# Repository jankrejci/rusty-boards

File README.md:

# Rusty Boards

Monorepo for ESP32 sensor boards and supporting services. KiCAD hardware
designs with embedded Rust firmware, plus a host-side metrics server.

Boards export Prometheus metrics over USB serial. The sensor-server collects
them and serves a combined `/metrics` endpoint for Prometheus scraping.

## Repository structure

```
boards/
  voltage-meter/        Voltage + temp + LCD board
    pcb/                KiCAD schematic and PCB
    firmware/           Embedded Rust (esp-hal, embassy)
  temp-sensor/          DS18B20 temperature sensor board
    firmware/           Embedded Rust (esp-hal, embassy)
  dummy-button/         Rotary encoder + USB-C power board
    pcb/                KiCAD schematic and PCB
    firmware/           Embedded Rust (esp-hal, embassy)
tools/
  sensor-server/        Host-side HTTP server bridging serial to Prometheus
lib/
  kicad/                Shared KiCAD symbols, footprints, and 3D models
```

## Boards

### voltage-meter

ADC voltage measurement with calibration curve and Kalman filter, LM75
temperature sensor over I2C, ST7735s 160x80 LCD display over SPI. Embassy
async tasks for reading, display, metrics export, and watchdog.

### temp-sensor

DS18B20 OneWire temperature sensors driven via the ESP32-C3 RMT peripheral.
Embassy async tasks for sensor reading, metrics export, and watchdog.

### dummy-button

Rotary encoder (PEC11R) with push button and TP5400 USB-C charging/boost
converter. ESP32-S3 (Xtensa) with hello world firmware.

## Tools

### sensor-server

HTTP server that auto-detects ESP32-C3 boards on USB (VID `0x303a`, PID
`0x1001`), reads Prometheus-formatted metrics from serial, and serves them on
`GET /metrics`. Uses inotify for instant device hot-plug detection.

## Hardware platform

Most boards use ESP32-C3 (RISC-V). dummy-button uses ESP32-S3 (Xtensa).

- ESP32-C3: target `riscv32imc-unknown-none-elf`, stable Rust, `build-std = ["core"]`
- ESP32-S3: target `xtensa-esp32s3-none-elf`, espup Xtensa toolchain
- Dev board: ESP32-C3 Super Mini, USB-JTAG on `/dev/ttyACM0`
- Flash/debug: probe-rs

## Development

Each project has its own nix flake with dev shells and checks.

```sh
cd boards/temp-sensor && nix develop     # firmware dev shell
cd boards/voltage-meter && nix develop   # firmware dev shell
cd boards/dummy-button && nix develop    # Xtensa firmware dev shell
cd boards/dummy-button && nix develop .#hardware  # KiCAD shell
cd tools/sensor-server && nix develop    # Rust dev shell
```

### Firmware workflow

```sh
cd boards/temp-sensor
nix develop
cd firmware
cargo build --release       # build
cargo run --release         # build + flash + monitor via probe-rs
```

### Static builds (sensor-server)

```sh
cd tools/sensor-server
nix develop .#x86_64-static     # x86_64 musl
nix develop .#aarch64-static    # aarch64 musl cross
cargo build --release
```

### Checks

Each flake defines checks that run with `nix flake check`:

| Project | Checks |
|---------|--------|
| `tools/sensor-server` | clippy, fmt, test |
| `boards/temp-sensor` | clippy, fmt |
| `boards/voltage-meter` | clippy, fmt, DRC, ERC |
| `boards/dummy-button` | DRC, ERC |

Cargo checks use [crane](https://github.com/ipetkov/crane). KiCAD checks use
`kicad-cli` for design rule checking (DRC) and electrical rule checking (ERC).

## Metrics format

All boards emit Prometheus text format over USB serial:

```
metric_name{label="value"} 42.0 1709500000000
```

The sensor-server validates, timestamps, and aggregates these lines for
Prometheus scraping.

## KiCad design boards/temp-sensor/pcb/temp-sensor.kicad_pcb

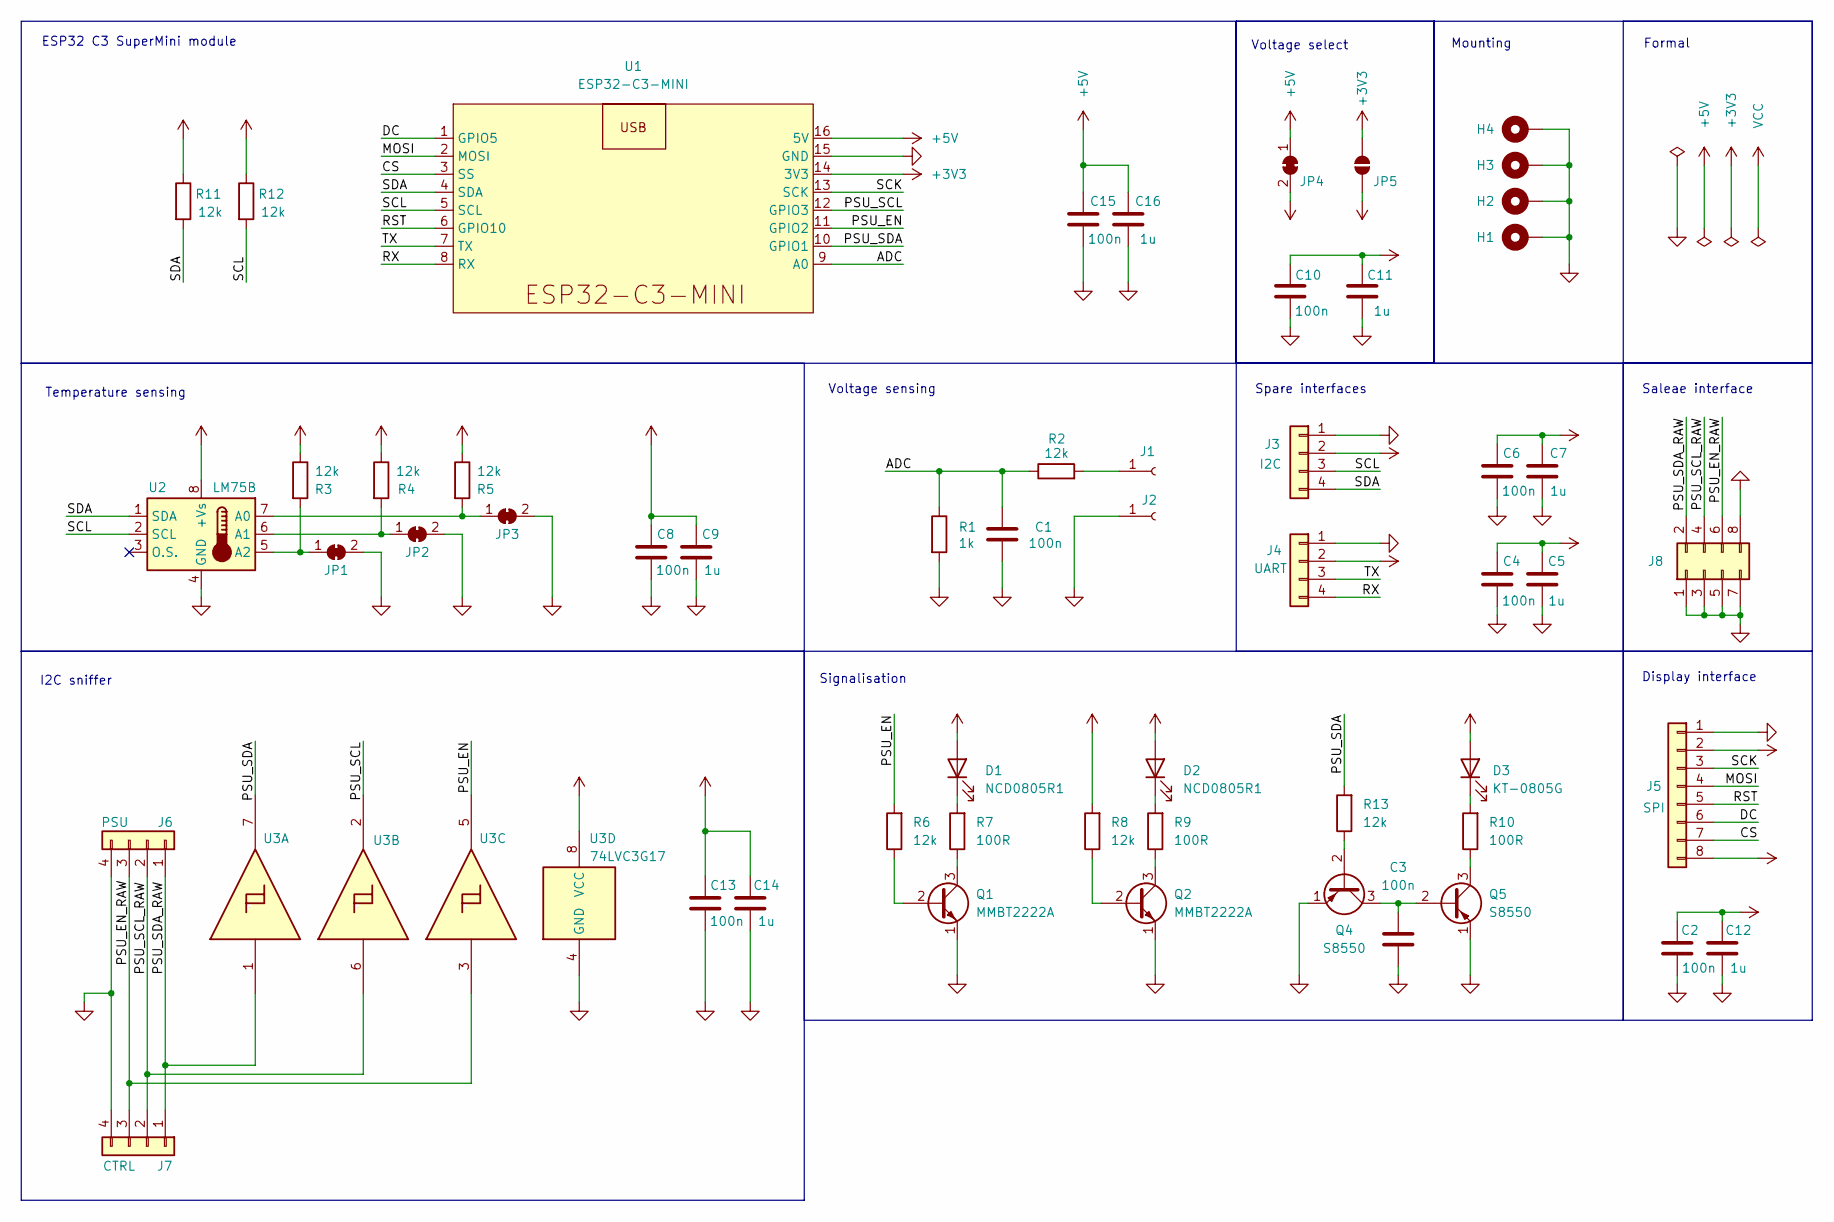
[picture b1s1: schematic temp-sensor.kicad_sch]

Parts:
C1, C2, C3, C4, C6, C8, C10, C13, C15: 100n; C_0603_1608Metric_Pad1.08x0.95mm_HandSolder; LCSC C14663
C5, C7: 1u; C_0603_1608Metric_Pad1.08x0.95mm_HandSolder; LCSC C59302
C9, C11, C12, C14, C16: 1u; C_0603_1608Metric_Pad1.08x0.95mm_HandSolder; LCSC C15849
D1, D2: NCD0805R1; LED_0805_2012Metric_Pad1.15x1.40mm_HandSolder; LCSC C84256
D3: KT-0805G; LED_0805_2012Metric_Pad1.15x1.40mm_HandSolder; LCSC C2297
H1, H2, H3, H4: M3_Pad_Via; MountingHole_3.2mm_M3_DIN965_Pad_TopBottom
J1: Bannana plug; Banana_Cliff_FCR7350R_S16N-PC_Horizontal
J2: Bannana plug; Banana_Cliff_FCR7350B_S16N-PC_Horizontal
J3: I2C; PinHeader_1x04_P2.54mm_Vertical
J4: UART; PinHeader_1x04_P2.54mm_Vertical
J5: SPI; PinHeader_1x08_P2.54mm_Vertical
J6: PSU; Molex_KK-254_AE-6410-04A_1x04_P2.54mm_Vertical
J7: CTRL; Molex_KK-254_AE-6410-04A_1x04_P2.54mm_Vertical
J8: Conn_02x08_Odd_Even; PinHeader_2x04_P2.54mm_Vertical
JP1, JP2, JP3, JP4: SolderJumper_2_Bridged; SolderJumper-2_P1.3mm_Bridged_RoundedPad1.0x1.5mm
JP5: SolderJumper_2_Open; SolderJumper-2_P1.3mm_Open_RoundedPad1.0x1.5mm
Q1, Q2: MMBT2222A; SOT-23; LCSC C8512
Q4, Q5: S8550; SOT-23; LCSC C105432
R1: 1k; R_0603_1608Metric_Pad0.98x0.95mm_HandSolder; LCSC C21190
R2, R3, R4, R5, R6, R8, R11, R12, R13: 12k; R_0603_1608Metric_Pad0.98x0.95mm_HandSolder; LCSC C22790
R7, R9, R10: 100R; R_0603_1608Metric_Pad0.98x0.95mm_HandSolder; LCSC C22775
U1: ESP32-C3-MINI; ESP32-C3-DevKitC-02
U2: LM75B; SOIC-8_3.9x4.9mm_P1.27mm; LCSC C725792
U3: 74LVC3G17; VSSOP-8_2.3x2mm_P0.5mm; LCSC C68245

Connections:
+3V3: JP5.2 (B), U1.14 (3V3)
+5V: C15.2, C16.2, JP4.1 (A), U1.16 (5V)
/ADC: C1.2, R1.1, R2.1, U1.9 (A0)
/CS: J5.7, U1.3 (SS)
/DC: J5.6, U1.1 (GPIO5)
/MOSI: J5.4, U1.2 (MOSI)
/PSU_EN: R6.2, U1.11 (GPIO2), U3.5
/PSU_EN_RAW: J6.3, J7.3, J8.6, U3.3
/PSU_SCL: U1.12 (GPIO3), U3.2
/PSU_SCL_RAW: J6.2, J7.2, J8.4, U3.6
/PSU_SDA: R13.2, U1.10 (GPIO1), U3.7
/PSU_SDA_RAW: J6.1, J7.1, J8.2, U3.1
/RST: J5.5, U1.6 (GPIO10)
/RX: J4.4, U1.8 (RX)
/SCK: J5.3, U1.13 (SCK)
/SCL: J3.3, R12.2, U1.5 (SCL), U2.2 (SCL)
/SDA: J3.4, R11.2, U1.4 (SDA), U2.1 (SDA)
/TX: J4.3, U1.7 (TX)
GND: C1.1, C2.1, C3.2, C4.1, C5.1, C6.1, C7.1, C8.1, C9.1, C10.1, C11.1, C12.1, C13.1, C14.1, C15.1, C16.1, H1.1, H2.1, H3.1, H4.1, J2.1, J3.1, J4.1, J5.1, J6.4, J7.4, J8.1, J8.3, J8.5, J8.7, J8.8, JP1.2 (B), JP2.2 (B), JP3.2 (B), Q1.1 (E), Q2.1 (E), Q4.1 (E), Q5.1 (E), R1.2, U1.15 (GND), U2.4 (GND), U3.4 (GND)
unnamed: D1.1 (K), R7.2
unnamed: D2.1 (K), R9.2
unnamed: D3.1 (K), R10.2
unnamed: J1.1, R2.2
unnamed: JP1.1 (A), R3.2, U2.5 (A2)
unnamed: JP2.1 (A), R4.2, U2.6 (A1)
unnamed: JP3.1 (A), R5.2, U2.7 (A0)
unnamed: Q1.2 (B), R6.1
unnamed: Q1.3 (C), R7.1
unnamed: Q2.2 (B), R8.1
unnamed: Q2.3 (C), R9.1
unnamed: Q4.2 (B), R13.1
unnamed: C3.1, Q4.3 (C), Q5.2 (B)
unnamed: Q5.3 (C), R10.1
VCC: C2.2, C4.2, C5.2, C6.2, C7.2, C8.2, C9.2, C10.2, C11.2, C12.2, C13.2, C14.2, D1.2 (A), D2.2 (A), D3.2 (A), J3.2, J4.2, J5.2, J5.8, JP4.2 (B), JP5.1 (A), R3.1, R4.1, R5.1, R8.2, R11.1, R12.1, U2.8 (+Vs), U3.8 (VCC)

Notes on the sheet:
Saleae interface
Signalisation
ESP32 C3 SuperMini module
Voltage sensing
I2C sniffer
Display interface
Voltage select
Formal
Spare interfaces
Mounting
Temperature sensing

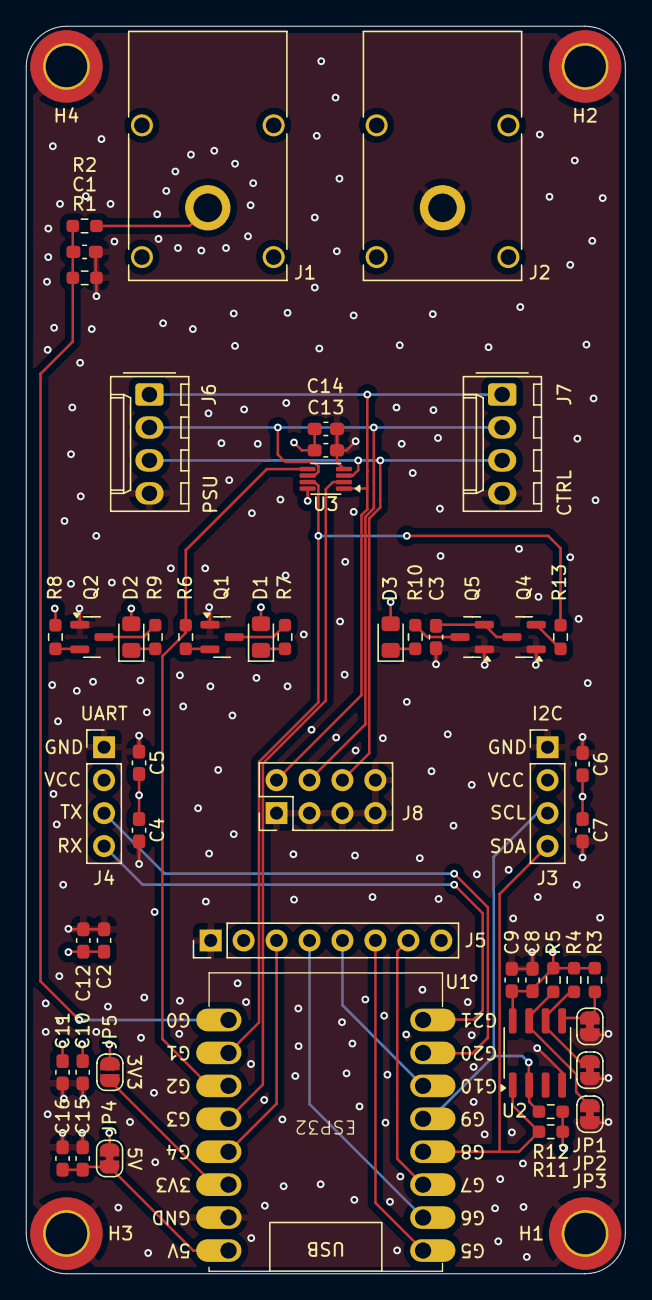
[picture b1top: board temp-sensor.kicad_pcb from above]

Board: 4 copper layers, 46.2 x 96.2 mm, 56 parts (0 on the bottom side), 34 nets.

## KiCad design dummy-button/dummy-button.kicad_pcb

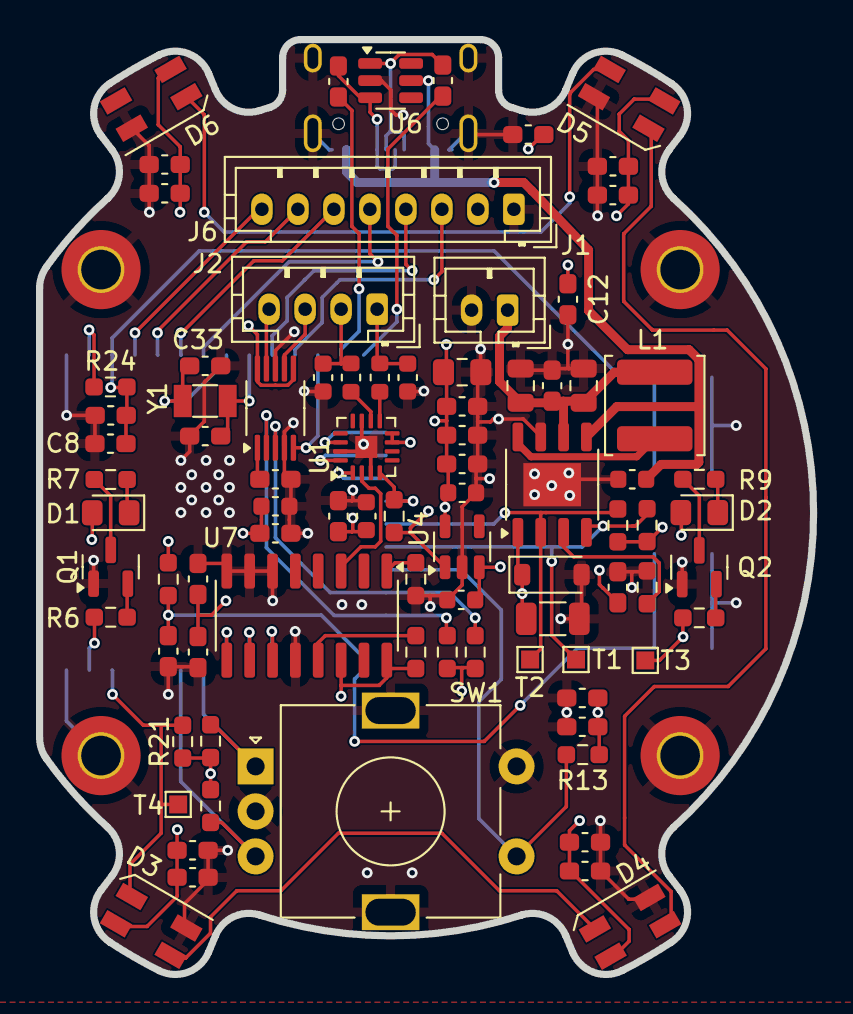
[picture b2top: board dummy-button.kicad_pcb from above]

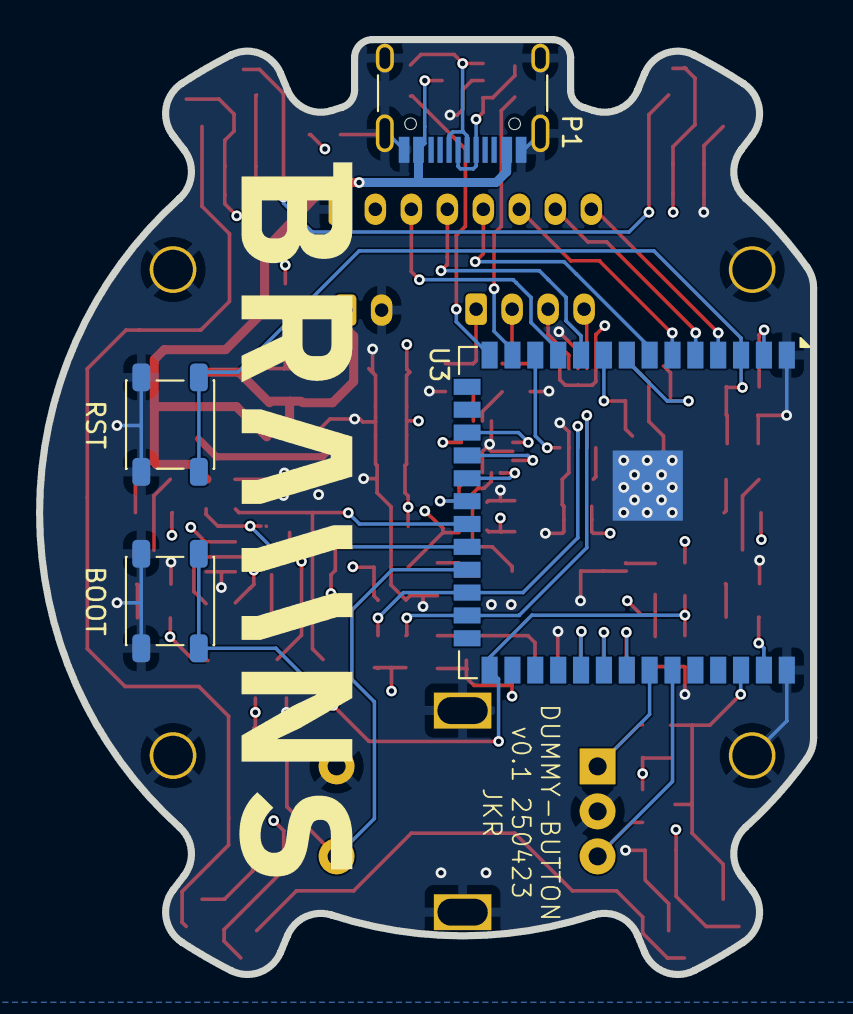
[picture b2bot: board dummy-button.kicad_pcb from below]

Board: 4 copper layers, 43.0 x 51.9 mm, 93 parts (4 on the bottom side), 57 nets.

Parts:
C2, C3, C4, C5, C6, C7, C8, C9, C10, C21, C22, C23, C24, C25, C30, C32: 100n; C_0603_1608Metric_Pad1.08x0.95mm_HandSolder
C12, C13, C14, C15, C16, C17, C18, C19, C28: 1u; C_0603_1608Metric_Pad1.08x0.95mm_HandSolder
C20: 4u7; C_0805_2012Metric_Pad1.18x1.45mm_HandSolder
C26, C29: 22u; C_0805_2012Metric
C27: 100u; C_1206_3216Metric
C31, C34, C35, C36, C39: 10u; C_0603_1608Metric
C33, C40: 12p; C_0603_1608Metric_Pad1.08x0.95mm_HandSolder
C37, C38: 220p; C_0603_1608Metric
D1, D2: NCD0805R1; LED_0805_2012Metric_Pad1.15x1.40mm_HandSolder
D3, D4, D5, D6: WS2812B; LED_SK6812MINI_PLCC4_3.5x3.5mm_P1.75mm
D7: TVS; D_SOD-123
FB1, FB2: FerriteBead_Small; L_0603_1608Metric
H1, H2, H3, H4: M2_Pad_Via; MountingHole_2.2mm_M2_Pad_TopOnly
J1: Batt; JST_PH_B2B-PH-K_1x02_P2.00mm_Vertical
J2: repro_motor; JST_PH_B4B-PH-K_1x04_P2.00mm_Vertical
J6: LCD; JST_PH_B8B-PH-K_1x08_P2.00mm_Vertical
L1: 10u; L_Sunlord_SWPA5040S
P1: USB_C_Plug_USB2.0; USB_C_Receptacle_HRO_TYPE-C-31-M-12
Q1, Q2: MMBT2222A; SOT-23
R6, R8, R11, R12, R13, R14, R15, R16, R19, R20, R21, R23, R24, R27: 12k; R_0603_1608Metric_Pad0.98x0.95mm_HandSolder
R7, R9: 100R; R_0603_1608Metric_Pad0.98x0.95mm_HandSolder
R17, R18: 10R; C_0603_1608Metric_Pad1.08x0.95mm_HandSolder
R25, R26: 100k; R_0603_1608Metric_Pad0.98x0.95mm_HandSolder
SW1: RotaryEncoder_Switch_MP; RotaryEncoder_Alps_EC11E-Switch_Vertical_H20mm
SW2: RST; SW_SPST_PTS647_Sx38
SW3: BOOT; SW_SPST_PTS647_Sx38
T1, T2, T3, T4: TestPoint; TestPoint_Pad_1.0x1.0mm
U1: MAX98357A; TQFN-16-1EP_3x3mm_P0.5mm_EP1.23x1.23mm
U2: TP5400; HTSOP-8-1EP_3.9x4.9mm_P1.27mm_EP2.4x3.2mm
U3: ESP32-S3-WROOM-1
U4: TLV75533PDBV; SOT-23-5
U5: DRV2605LDGS; VSSOP-10_3x3mm_P0.5mm
U6: ESDU5V0H4; SOT-23-6
U7: CD4051B; SOIC-16_3.9x9.9mm_P1.27mm
Y1: 32.768 kHz; Crystal_SMD_3215-2Pin_3.2x1.5mm

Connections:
+3V3: C2.2, C3.2, C12.2, C13.2, C20.1, C21.1, C22.1, C23.1, C35.1, J6.2, R8.2, R11.1, R12.1, R13.1, R14.1, R15.1, R16.1, R20.1, R21.1, R24.1, R27.1, T3.1, U3.2 (3V3), U4.5 (OUT)
+5V: C4.2, C5.2, C6.2, C7.2, C9.2, C14.2, C15.2, C16.2, C17.2, C25.1, C27.1, C28.2, C30.1, C32.1, C34.1, C36.1, C39.1, D1.2 (A), D2.2 (A), D3.4 (VDD), D4.4 (VDD), D5.4 (VDD), D6.4 (VDD), D7.1 (K), R23.1, R25.2, U1.7 (VDD), U1.8 (VDD), U2.1 (VOUT), U4.1 (IN), U4.3 (EN), U5.6 (VDD/NC), U5.10 (VDD), U7.14 (X1), U7.16 (VDD)
/CPU/BAT_CHRG: R20.2, T2.1, U2.2 (CHRG), U3.21 (IO13)
/CPU/BAT_STDBY: R16.2, T1.1, U2.4 (STDBY), U3.22 (IO14)
/CPU/BOOT: C10.1, R27.2, SW3.1, U3.27 (IO0)
/CPU/DM: R18.1, U3.13 (USB_D-)
/CPU/DP: R17.1, U3.14 (USB_D+)
/CPU/EN: C8.1, C19.1, R24.2, SW2.1, U3.3 (EN)
/CPU/GAIN_A: U3.31 (IO38), U7.11 (A)
/CPU/GAIN_B: U3.32 (IO39), U7.10 (B)
/CPU/GAIN_C: U3.33 (IO40), U7.9 (C)
/CPU/HEARTBEAT: R6.2, U3.39 (IO1)
/CPU/LCD_BLK: J6.8, U3.4 (IO4)
/CPU/LCD_CS: J6.7, U3.5 (IO5)
/CPU/LCD_DC: J6.6, U3.6 (IO6)
/CPU/LCD_MOSI: J6.4, U3.10 (IO17)
/CPU/LCD_RST: J6.5, U3.7 (IO7)
/CPU/LCD_SCK: J6.3, U3.11 (IO18)
/CPU/LED_BUS: D3.3 (DIN), R21.2, T4.1, U3.38 (IO2)
/CPU/MOTOR_EN: U3.12 (IO8), U5.5 (EN)
/CPU/REPRO_CLK: U1.16 (BCLK), U3.18 (IO10)
/CPU/REPRO_SD: U1.1 (DIN), U3.19 (IO11)
/CPU/REPRO_SD_MODE: R23.2, U1.4 (~SD_MODE), U3.20 (IO12)
/CPU/REPRO_WS: U1.14 (LRCLK), U3.17 (IO9)
/CPU/ROT_A: R14.2, SW1.A, U3.34 (IO41)
/CPU/ROT_B: R15.2, SW1.B, U3.35 (IO42)
/CPU/ROT_SW: R13.2, SW1.S1, U3.23 (IO21)
/CPU/SCL: R12.2, U3.25 (IO48), U5.2 (SCL)
/CPU/SDA: R11.2, U3.24 (IO47), U5.3 (SDA)
/CPU/XTAL_A: C33.2, U3.8 (IO15), Y1.2
/CPU/XTAL_B: C40.2, U3.9 (IO16), Y1.1
/Peripherals/MOTOR_N: J2.4, U5.9 (OUT-)
/Peripherals/MOTOR_P: J2.3, U5.7 (OUT+)
/Peripherals/REPRO_GAIN: U1.2 (GAIN_SLOT), U7.3 (X)
/Peripherals/REPRO_N: C38.1, FB1.1, J2.2
/Peripherals/REPRO_P: C37.1, FB2.1, J2.1
GND: C2.1, C3.1, C4.1, C5.1, C6.1, C7.1, C8.2, C9.1, C10.2, C12.1, C13.1, C14.1, C15.1, C16.1, C17.1, C18.1, C19.2, C20.2, C21.2, C22.2, C23.2, C24.2, C25.2, C26.2, C27.2, C28.1, C29.2, C30.2, C31.2, C32.2, C33.1, C34.2, C35.2, C36.2, C37.2, C38.2, C39.2, C40.1, D3.2 (VSS), D4.2 (VSS), D5.2 (VSS), D6.2 (VSS), D7.2 (A), H1.1, H2.1, H3.1, H4.1, J1.2, J6.1, P1.A1 (GND), P1.A12 (GND), P1.B1 (GND), P1.B12 (GND), P1.S1 (SHIELD), Q1.1 (E), Q2.1 (E), R19.2, R26.2, SW1.C, SW1.MP, SW1.S2, SW2.2, SW3.2, U1.3 (GND), U1.11 (GND), U1.15 (GND), U1.17 (PAD), U2.7 (GND), U2.9 (PAD), U3.1 (GND), U3.40 (GND), U3.41 (GND), U4.2 (GND), U5.4 (IN/TRIG), U5.8 (GND), U6.2 (GND), U7.6 (INH), U7.7 (VEE), U7.8 (VSS), U7.12 (X3)
unnamed: D1.1 (K), R7.2
unnamed: D2.1 (K), R9.2
unnamed: D3.1 (DOUT), D4.3 (DIN)
unnamed: D4.1 (DOUT), D5.3 (DIN)
unnamed: D5.1 (DOUT), D6.3 (DIN)
unnamed: C24.1, C26.1, C29.1, J1.1, L1.2, U2.6 (BAT)
unnamed: Q1.2 (B), R6.1
unnamed: Q1.3 (C), R7.1
unnamed: Q2.2 (B), R8.1
unnamed: Q2.3 (C), R9.1
unnamed: FB1.2, U1.10 (OUTN)
unnamed: FB2.2, U1.9 (OUTP)
unnamed: L1.1, U2.8 (LX)
unnamed: R19.1, U2.3 (PROG)
unnamed: C18.2, U5.1 (REG)
unnamed: P1.A6 (D+), P1.B6 (D+), R17.2, U6.1 (I/O1)
unnamed: P1.A7 (D-), P1.B7 (D-), R18.2, U6.3 (I/O2)
unnamed: R25.1, U7.13 (X0)
unnamed: R26.1, U7.1 (X4)
VBUS: C31.1, P1.A4 (VBUS), P1.A9 (VBUS), P1.B4 (VBUS), P1.B9 (VBUS), U2.5 (VCC), U6.5 (VBUS)

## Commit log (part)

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2024-12-03 Initialize the repository
2024-12-19 WIP Introduce the voltage meter board
2025-04-23 Revert "Introduce dummy button board"
2025-04-23 Voltage meter manufacturing improvements
2025-05-13 Refactor the dummy button to separate power source
2025-05-15 Add path export for nushell
2025-05-19 voltage-meter: Generate template project for the ESP32-C3
2025-05-20 voltage-meter: Adjust the template structure
2025-05-20 voltage-meter: Add rust tools
2025-05-20 voltage-meter: Integrate metrics module
2025-05-21 voltage-meter: Integrate watchdog support
2025-05-21 voltage-meter: Add adc reader module
2025-05-21 voltage-meter: Rename temperature example to lm75_reader
2025-05-21 voltage-meter: Rename MetricsHandler to MetricsExporter
2025-05-28 voltage-meter: Introduce the display module
    - show measured voltage and temperature
2026-02-26 rusty-boards: Add Claude Code configuration
    - add CLAUDE.md with project role, principles, workflow, and communication guidelines
    - add .claude/rules/firmware.md with embedded firmware guidelines (path-targeted)
    - add .claude/rules/git.md with commit format and branch cleanup rules
    - add skill definitions for commit, branch-cleanup, flash, and review-branch
2026-02-26 rusty-boards: Add Rust firmware CI pipeline
    - run gitlint commit message validation on PRs
    - matrix build for firmware crates with fmt, clippy, check, and release build
    - use stable toolchain with build-std via cargo unstable config
2026-02-26 rusty-boards: temp-sensor: Add DS18B20 firmware
    - add OneWire RMT bus driver with bit-banged timing on ESP32-C3
    - add DS18B20 sensor discovery, conversion trigger, and temperature read
    - add Prometheus metrics export over USB-serial via esp_println
    - add cooperative watchdog with hardware WDT reset on sensor stall
    - add config module with hardware and runtime constants
2026-02-26 rusty-boards: temp-sensor: Add firmware scaffold
    - add Cargo.toml with esp-hal, embassy, and defmt dependencies
    - configure probe-rs runner and riscv32imc target in .cargo/config.toml
    - add build.rs with linker error diagnostics for defmt and linkall.x
    - pin stable toolchain with riscv32imc target in rust-toolchain.toml
2026-02-26 rusty-boards: Add gitlint commit message validation
    - enforce rusty-boards module prefix format in title
    - require bullet-point body format with custom UC1 rule
    - reject banned content lines and emojis with UC2 rule
2026-02-26 rusty-boards: Add treefmt-nix formatter
    - add root flake with treefmt-nix for rustfmt and nixfmt
    - add formatting check via nix flake check
2026-02-27 rusty-boards: Rework review-branch skill and add fix-review skill
    - rewrite review-branch to produce structured findings with severity levels
    - add fix-review skill for applying review fixes as fixup commits
    - add /fix-review entry to CLAUDE.md skills table
2026-03-02 rusty-boards: temp-sensor: Improve firmware
    - extract DS18B20 driver and OneWire bus into separate modules
    - add build.rs for linker configuration
    - add config module for compile-time settings
    - add metrics module for Prometheus exposition format
2026-03-02 rusty-boards: sensor-server: Add serial-to-HTTP metrics bridge
    - add host-side service that reads metrics from ESP32-C3 over serial
    - auto-discover sensor boards via USB vendor/product ID
    - parse Prometheus exposition format from serial output
    - serve collected metrics over HTTP for Prometheus scraping
    - add flake.nix for nix-based development environment
2026-03-02 rusty-boards: sensor-server: Add lock files
    - add Cargo.lock for reproducible builds
    - add flake.lock for pinned nix dependencies
2026-03-02 rusty-boards: voltage-meter: Update PCB for manufacturing
    - bump board revision to v0.2
    - update trace routing and via placement
2026-03-02 rusty-boards: Add shared footprint library from njordr
    - add rusty-boards.pretty with R-0603-HandSolder, C-0603-HandSolder,
    and SOT-23 footprints copied from njordr
    - add 3D step models for R-0603, C-0603, and SOT-23 to
    components/packages
    - register rusty-boards library in voltage-meter fp-lib-table
2026-03-02 rusty-boards: voltage-meter: Reassign footprints to shared library
    - reassign R1-R13 from Resistor_SMD to rusty-boards:R-0603-HandSolder
    - reassign C1-C16 from Capacitor_SMD to rusty-boards:C-0603-HandSolder
    - reassign Q1-Q5 from Package_TO_SOT_SMD to rusty-boards:SOT-23
    - exclude remaining lib_footprint_mismatch for D1-D3 and J6-J7
    - remove stale DRC exclusions for replaced footprints
2026-03-02 rusty-boards: voltage-meter: Add firmware project scaffold
    - Cargo.toml with esp-hal, embassy, defmt dependencies
    - Build script for linker configuration
    - Cargo and Helix editor configuration
    - Rust toolchain pinned to stable with riscv32imc target
    - lib.rs re-exporting module structure
2026-03-02 rusty-boards: voltage-meter: Add Prometheus metrics module
    - PubSub-based metrics channel with create_metrics! macro
    - MetricsExporter task prints Prometheus text format via esp-println
    - metrics_exporter example for standalone testing
2026-03-02 rusty-boards: voltage-meter: Add ST7735s display module
    - SPI-based display driver with text rendering
    - Hardware pin configuration in config module
    - animation example for standalone display testing
2026-03-02 rusty-boards: voltage-meter: Add watchdog example
    - Demonstrates cooperative task-level watchdog pattern
2026-03-02 rusty-boards: voltage-meter: Add lock file
2026-03-04 rusty-boards: Reorganize into boards/, tools/, lib/ structure
    - move board projects under boards/<name>/pcb/ and boards/<name>/firmware/
    - move shared KiCAD library from components/ to lib/kicad/
    - move sensor-server under tools/
    - update KiCAD lib-table paths and CI workflow paths
2026-03-04 rusty-boards: sensor-server: Add crane checks to flake
    - add crane input for build/check infrastructure
    - add clippy, fmt, and test checks via crane
2026-03-04 rusty-boards: dummy-button: Add Nix flake with Xtensa dev shell
    - espup-based Xtensa toolchain install with NixOS binary patching
    - firmware and hardware (KiCAD) dev shells
    - DRC and ERC nix checks via kicad-cli
2026-03-04 rusty-boards: Move board flakes to board root with crane checks
    - move temp-sensor flake.nix from firmware/ to board root
    - add voltage-meter flake.nix at board root
    - add crane-based clippy and fmt checks to both boards
    - voltage-meter flake adds DRC/ERC checks and hardware dev shell
    - no_std incompatibility with crane's buildDepsOnly documented in comments
2026-03-04 rusty-boards: Add lock files
    - dummy-button firmware Cargo.lock
    - dummy-button flake.lock (moved from temp-sensor/firmware/)
    - temp-sensor and voltage-meter board-level flake.lock
    - update sensor-server flake.lock with crane input
2026-03-04 rusty-boards: Refactor AI config into CLAUDE.md and AGENTS.md
    - slim down root CLAUDE.md and sensor-server CLAUDE.md to role/rules only
    - add AGENTS.md files with project descriptions, architecture, dev commands
    - add root AGENTS.md with repo structure and hardware platform overview
    - update git rules to include AGENTS.md in config separation rule
    - update firmware rules path targeting
2026-03-04 rusty-boards: Expand branch-cleanup skill with rebase ops
    - add split, reorder, move-files, and drop operations using GIT_SEQUENCE_EDITOR
    - restructure into Step 0 (backup) -> Operation -> Final Step (verify) flow
    - move soft reset to last resort position
    - add lock file separation to principles
2026-03-04 rusty-boards: Expand review-branch skill to exhaustive CI-ready review
    - run cargo check, clippy, fmt --check for every affected crate
    - run nix flake check for every board/tool with a flake
    - verify commit message claims match actual diffs
    - add cross-cutting checks for integration, paths, toolchain files
    - require exhaustive findings so branch is merge-ready after one pass
2026-03-04 rusty-boards: sensor-server: Add systemd service file
    - DynamicUser sandboxing with dialout group for serial access
    - RUST_LOG env var for log verbosity control
    - auto-restart on failure with 5s delay
2026-03-04 rusty-boards: sensor-server: Add nix package and deb outputs
    - packages.default: static musl binary via pkgsStatic.rustPlatform
    - packages.deb: debian package built with nfpm
    - deb includes binary, systemd service, and maintainer scripts
    - version read from Cargo.toml automatically
    - postinst enables and starts the service on install
    - add package and deb builds to flake checks on linux
2026-03-06 rusty-boards: Centralize cargo build artifacts into build/
    - add target-dir to each project .cargo/config.toml pointing to
    build/<project>/target/ relative to repo root
    - create tools/sensor-server/.cargo/config.toml for target-dir
    - add build/ to .gitignore alongside existing target/ entry
2026-03-06 rusty-boards: temp-sensor: Add PCB design files
    - copy voltage-meter KiCad project as starting point
    - rename all files and internal references to temp-sensor
2026-03-14 rusty-boards: miner-scraper: Add nix packaging and systemd service
    - nix flake enables reproducible static musl builds for debian deployment
    - systemd manages lifecycle with journald logging
    - listens on all interfaces so prometheus can reach the exporter
2026-03-14 rusty-boards: Adopt agent rules
    - git-absorb, GIT_SEQUENCE_EDITOR, and multi-phase analysis for branch cleanup
    - model routing prevents wasting opus tokens on grunt work
    - WHY-not-WHAT commit philosophy produces more useful history
2026-03-14 rusty-boards: miner-scraper: Add flake.lock
2026-03-14 rusty-boards: miner-scraper: Add README
    - no documentation existed for build, config, or usage
2026-03-14 fixup! rusty-boards: miner-scraper: Add metrics exporter
2026-03-15 rusty-boards: miner-scraper: Add and update API response dumps
    - comprehensive reference data needed for parser development and testing
    - documents actual field names and structures across all firmware variants
2026-03-15 rusty-boards: miner-scraper: Clean up config, store, and scraper manager
    - config intervals use Duration directly instead of converting from raw u64
    - store methods only used in tests get #[cfg(test)] gating
    - host removal on target deletion goes through the metrics channel instead of
    direct store access, removing the store dependency from manage_scrapers
2026-03-15 rusty-boards: miner-scraper: Add trait-based parser pipeline and HTTP endpoints
    - endpoint fetch returns Response enum (Json/Text) instead of raw serde Value,
    enabling non-JSON protocols through the same pipeline
    - HTTP fetch with reqwest for stock firmware port 6060 text endpoints
    - Parser trait abstracts JsonParser and new PlainParser for regex-based text
    extraction (readvol: voltage, feedback, power status)
    - scraper dispatches to the appropriate parser based on response type
2026-03-15 rusty-boards: miner-scraper: Extract ScraperManager from main
    - scraper lifecycle logic belongs with the scraper module, not main
    - main.rs becomes pure wiring with no domain logic
2026-03-15 fixup! rusty-boards: miner-scraper: Split Store into Store and StoreHandle
2026-03-15 rusty-boards: miner-scraper: Rename StoreHandle to StoreState
    - "handle" suggests a resource manager, "state" better describes shared read-only data
2026-03-15 rusty-boards: miner-scraper: Wire config channel into ConfigFile, simplify task shutdown
    - ConfigFile owns the watch sender, removing the need to thread it separately
    - channel created with default config, real config published after CLI overrides
    - background tasks collected in a Vec and aborted uniformly on shutdown
2026-03-15 rusty-boards: miner-scraper: Abort child scrapers on manager drop, name channel const
    - ScraperManager now owns its task map and implements Drop to abort children
    - prevents orphaned scraper tasks from making requests after shutdown
    - extract METRICS_CHANNEL_SIZE const, rename cfg to config
2026-03-15 rusty-boards: miner-scraper: Add tokio-util dependency
    - needed for CancellationToken-based graceful shutdown
2026-03-15 rusty-boards: miner-scraper: Rename channel variables to sender/receiver
    - tx/rx suffixes are cryptic, sender/receiver is self-documenting
2026-03-15 rusty-boards: miner-scraper: Add tokio-stream dependency and Hash on Endpoint
    - StreamMap needs Hash on its key type for per-endpoint interval tracking
    - tokio-stream "time" feature provides IntervalStream wrapper
